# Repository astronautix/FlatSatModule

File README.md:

# Introduction

This KiCAD project is part of the Astronautix FlatSat project, which aims to create an extensible platform for nanosatellite subsystem prototyping and experimentation.

The FlatSat platform is composed of a main metallic support plate, which can possibly host 8 submodules in star configuration. Each submodule is composed of a STM32F429IDISCOVERY board and a custom adapter hat (**this project**).

All modules are hooked to a central hub via a sub-d DB26HD harness. The central hub has the main purpose of routing UART signals, regulating power (dispatched via sub-d, switchable) and linking all submodules together.

# The IonSat FlatSat Module

The adapter hats has the primary purpose of routing all the needed bus signal from the STM32 board to the sub-d connector. As an added bonus, a microSD connector has been inserted to provide autonomous data storage, and a breakout header is provided for signal debugging purposes. Two LEDs are present, one to signal for the powering of the board, and the other for the SD card detection. Finally, a jumper is provided for 5V sub-d cutoff if needed (we might want to bring power through USB directly)

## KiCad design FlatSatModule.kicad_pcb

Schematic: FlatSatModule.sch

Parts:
D1, D2: LED; LED_0805_2012Metric_Pad1.15x1.40mm_HandSolder
G1: LOGO; X-LOGO
H1, H2, H3, H4: MountingHole_Pad; MountingHole_2.2mm_M2_Pad
J1: DB26_Male_HighDensity_MountingHoles; DSUB-26-HD_Male_Horizontal_P2.29x1.98mm_EdgePinOffset8.35mm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
J2: Micro_SD_Card_Det; microSD_HC_Hirose_DM3AT-SF-PEJM5
J3: HEADER_13x2; PinHeader_2x13_P2.54mm_Vertical
JP1: Jumper_2_Bridged; PinHeader_1x02_P2.54mm_Vertical
R1, R2, R101: R; R_0603_1608Metric_Pad1.05x0.95mm_HandSolder
stm32101: STM32F429i-Discovery; stm32f429i-disco

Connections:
/5V: J3.1, JP1.1, stm32101.1 (5V), stm32101.2 (5V)
/CAN1_RX: J1.14, J3.13, stm32101.50 (A11)
/CAN1_TX: J1.5, J3.11, stm32101.49 (A12)
/I2C1_SCL: J1.19, J3.23, stm32101.19 (B8)
/I2C1_SDA: J1.10, J3.25, stm32101.24 (B7)
/I2C2_SCL: J1.20, J3.26, stm32101.112 (B10)
/I2C2_SDA: J1.1, J3.24, stm32101.111 (B11)
/SD_CLK: J2.5 (CLK), stm32101.43 (C12)
/SD_CMD: J2.3 (CMD), stm32101.40 (D2)
/SD_D0: J2.7 (DAT0), stm32101.55 (C8)
/SD_D1: J2.8 (DAT1), stm32101.54 (C9)
/SD_D2: J2.1 (DAT2), stm32101.45 (C10)
/SD_D3: J2.2 (DAT3/CD), stm32101.44 (C11)
/SD_DET: D2.2 (A), J2.9 (DET_B), R101.1, stm32101.35 (D7)
/SPI1_MISO: J1.2, J3.19, stm32101.25 (B4)
/SPI1_MOSI: J1.12, J3.17, stm32101.87 (A7)
/SPI1_SCK: J1.11, J3.21, stm32101.85 (A5)
/SPI1_SS: J1.3, J3.15, stm32101.86 (A4)
/SPI4_MISO: J1.13, J3.20, stm32101.14 (E5)
/SPI4_MOSI: J1.22, J3.22, stm32101.11 (E6)
/SPI4_SCK: J1.21, J3.18, stm32101.15 (E2)
/SPI4_SS: J1.4, J3.16, stm32101.13 (E4)
/UART1_RX: J1.23, J3.12, stm32101.51 (A10)
/UART1_TX: J1.15, J3.14, stm32101.52 (A9)
/UART2_RX: J1.6, J3.7, stm32101.83 (A3)
/UART2_TX: J1.24, J3.9, stm32101.84 (A2)
GND: H1.1, H2.1, H3.1, H4.1, J1.0, J1.18, J2.6 (VSS), J2.11 (SHIELD), J3.2, R1.2, R2.2, R101.2, stm32101.63 (GND), stm32101.64 (GND), stm32101.75 (GND), stm32101.93 (GND), stm32101.127 (GND), stm32101.128 (GND)
unnamed: D1.1 (K), R1.1
unnamed: D2.1 (K), R2.1
unnamed: J1.9, JP1.2
VCC: D1.2 (A), J1.8, J2.4 (VDD), J2.10 (DET_A), J3.4, stm32101.65 (3V), stm32101.66 (3V)

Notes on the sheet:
STM32F429IDISCOVERY headers
Peripherals
CSEP Flatsat : STM32F429IDISCOVERY Hat
July 2020
Reference pinout
1.0
Connectors

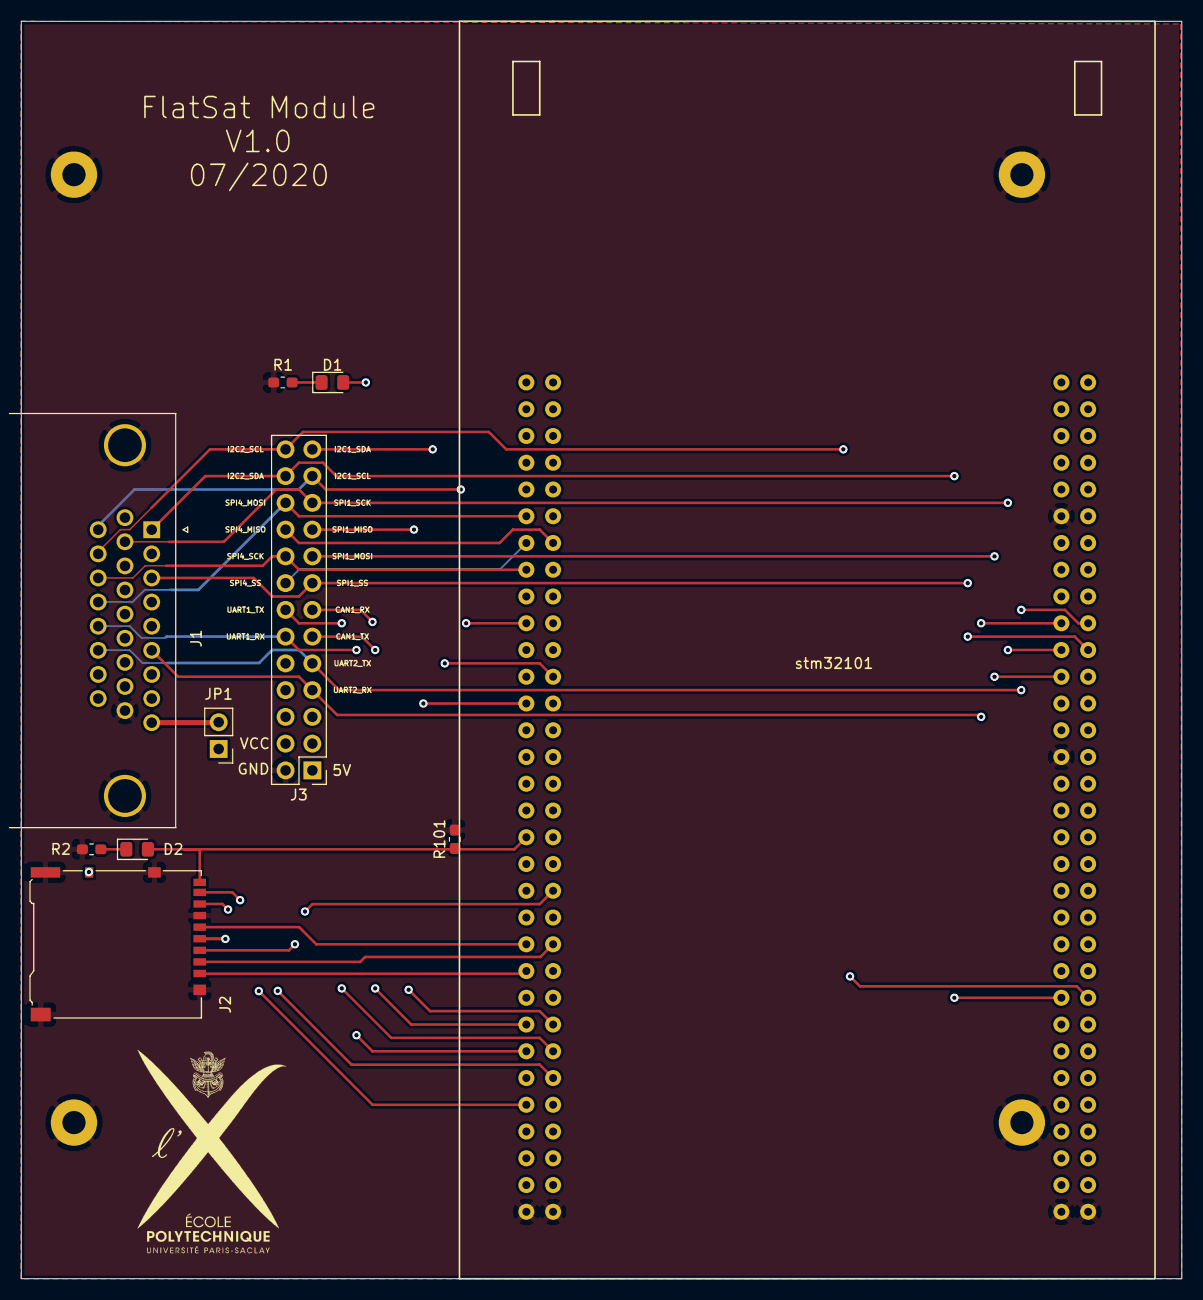
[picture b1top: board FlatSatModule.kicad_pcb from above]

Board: 4 copper layers, 110.2 x 119.4 mm, 15 parts (0 on the bottom side), 31 nets.

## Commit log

2020-06-24 first init
2020-06-30 first routing, lost schematic
2020-06-30 recovered schematic
2020-07-07 updated wiring + wired SD card
2020-07-07 add reference pinout
2020-07-07 add USARTs and gnd plane filling
2020-07-07 Add SS for SPI buses
2020-07-08 clarify schematic
2020-07-10 Redo routing
2020-07-10 add freecad file
2020-07-13 Fix track size
2020-07-13 Added silkscreen text
2020-07-14 improve schematic and replace footprints
2020-07-14 Add mounting holes, replace microSD footprint and move components
2020-07-14 redact readme
2020-07-14 Add plate plan to readme
2020-07-14 Replaced DB 26 HD footprint, cleaned layout and few fixes...
2020-07-14 Import modifications from jeandet/FlatSatModule
2020-07-15 Add X logo, reset version to 1.0 and move microSD label
2020-07-15 wire sd_det to stm32 and correct stm32 footprint
2020-07-16 Added pull down resistor for SD card detect and few track clean.
2020-09-14 improve readme
